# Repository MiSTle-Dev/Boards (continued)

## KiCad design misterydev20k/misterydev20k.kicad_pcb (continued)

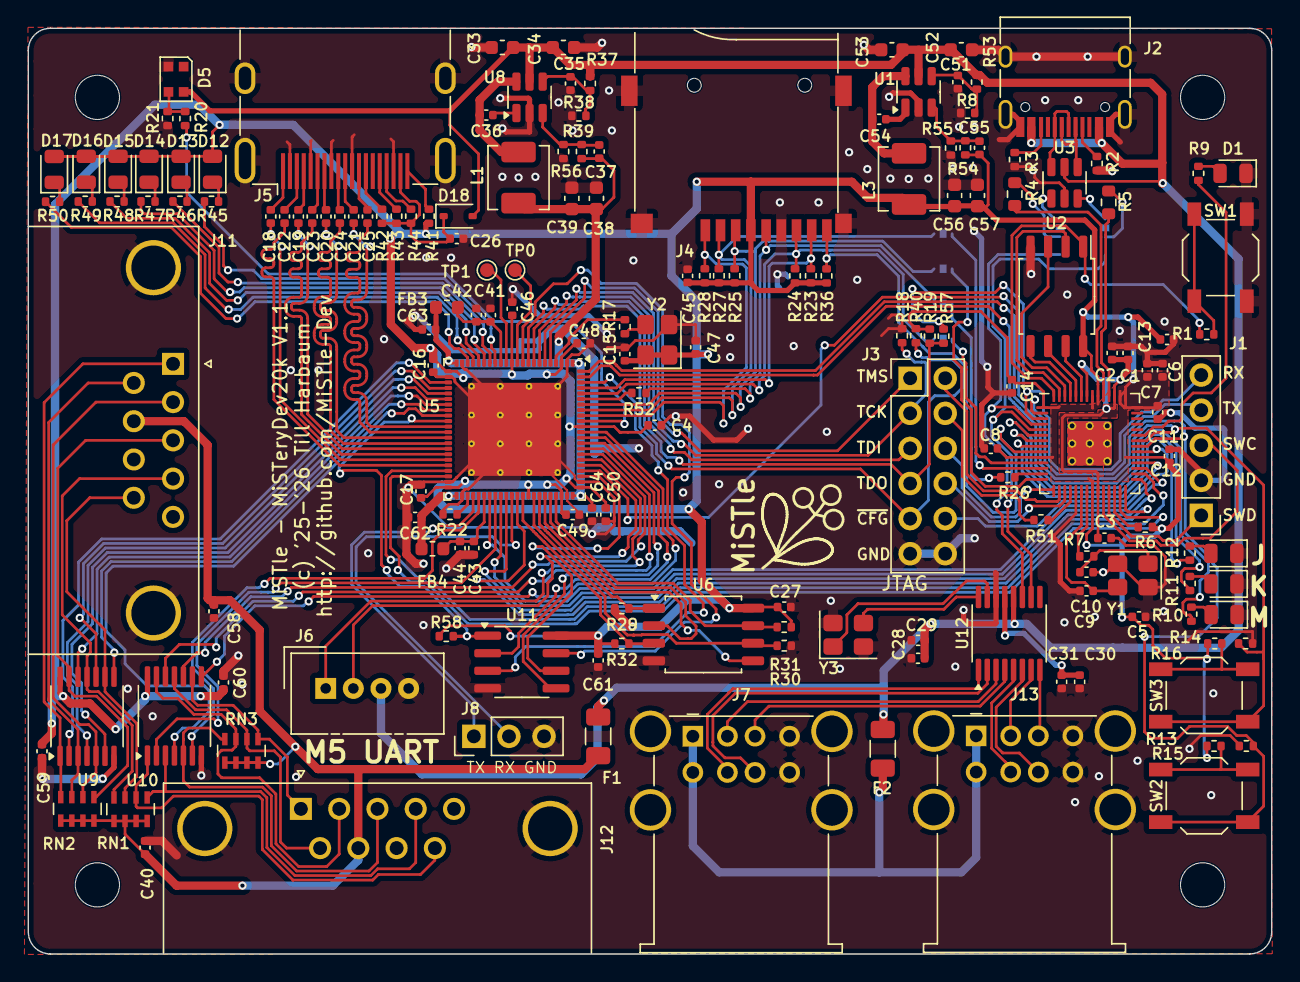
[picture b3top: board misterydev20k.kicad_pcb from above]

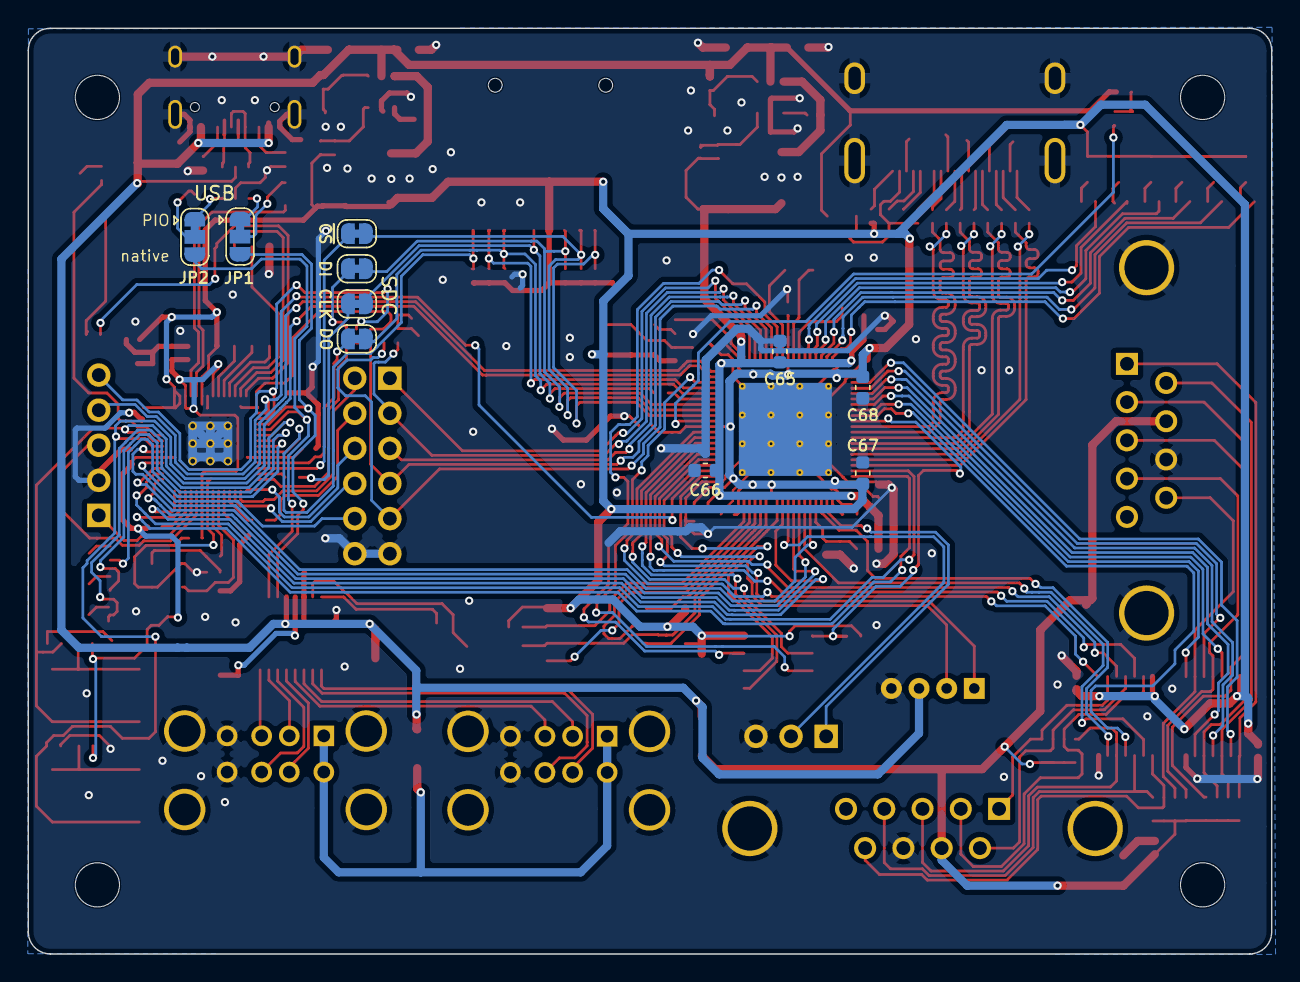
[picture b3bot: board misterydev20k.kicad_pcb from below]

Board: 2 copper layers, 90.0 x 67.0 mm, 183 parts (10 on the bottom side), 177 nets.

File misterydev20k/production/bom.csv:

Designator,Footprint,Quantity,Value,LCSC Part #
"C1, C29, C6, C8",0402,4,1uF,C52923
"C10, C37, C55, C9",0402,4,22pF,C1555
"C11, C12, C13, C14, C15, C16, C17, C18, C19, C2, C20, C21, C22, C23, C24, C25, C26, C27, C28, C3, C30, C35, C36, C4, C40, C42, C44, C45, C46, C47, C48, C49, C5, C50, C51, C54, C58, C59, C60, C61, C62, C63, C64",0402,43,100nF,C1525
"C31, C41, C43, C7",0402,4,10uF,C15525
"C33, C53",0603,2,10uF,C19702
"C34, C39, C52, C57",0603,4,100nF,C14663
"C38, C56",0603,2,22uF,C84419
"D1, D12, D13, D14, D15, D16, D17",0805,7,green,C2297
D18,D_SOD-323,1,1N5819WS,C191023
D2,0805,1,Mouse,C2297
D3,0805,1,Keyboard,C2297
D4,0805,1,Joystick,C2297
D5,LED_WS2812B-2020_PLCC4_2.0x2.0mm,1,WS2812B-2020,C965555
"F1, F2",1206,2,500mA,C70076
"FB3, FB4",0603,2,MPZ1608S101,C107332
J1,PinHeader_1x05_P2.54mm_Vertical,1,SWD,C492404
J11,DSUB-9_Pins_Horizontal_P2.77x2.84mm_EdgePinOffset7.70mm_Housed_MountingHolesOffset9.12mm,1,Joystick 0,C141880
J12,DSUB-9_Pins_Horizontal_P2.77x2.84mm_EdgePinOffset7.70mm_Housed_MountingHolesOffset9.12mm,1,Joystick 1,C141880
"J13, J7",USB_A_Wuerth_61400826021_Horizontal_Stacked,2,USB_A_Stacked,C456021
J2,USB_C_Receptacle_HRO_TYPE-C-31-M-12,1,USB_C_Receptacle_USB2.0,C165948
J3,PinHeader_2x06_P2.54mm_Vertical,1,Jumper block,C32713279
J4,TF-015,1,Micro_SD_Card_Det1,C393941
J5,HDMI_A_Molex_208658-1001_Horizontal,1,HDMI_A,C720616
"L1, L3",L_Sunlord_MWSA0402S,2,3.3uH,C408336
"R1, R15, R16, R30, R6, R7",0402,6,1k,C11702
"R10, R11, R12, R45, R46, R47, R48, R49, R50, R57, R9",0402,11,560,C163460
"R13, R14",0402,2,330,C105875
"R17, R26, R51, R52",0402,4,22,C25092
"R18, R19, R29, R31, R32, R40, R58",0402,7,4k7,C25900
"R2, R3",0402,2,5k1,C25905
R20,0402,1,100,C25076
"R21, R22, R23, R24, R25, R27, R28, R36, R41, R42, R43, R44",0402,12,10k,C25744
"R37, R53",0402,2,47k,C11702
"R38, R8",0402,2,30k,C138008
R39,0402,1,12k 1%,C25752
"R4, R5",0603,2,27R,C25190
R54,0402,1,15k 1%,C25756
R55,0402,1,3k3 1%,C25890
R56,0402,1,18k 1%,C138044
"RN1, RN2, RN3",R_Array_Concave_4x0603,3,10k,C110924
SW1,SW_SPST_TL3342,1,Boot,C318884
SW2,SW_SPST_TL3342,1,KEY1,C318884
SW3,SW_SPST_TL3342,1,KEY2,C318884
"U1, U8",TSOT-23-6,2,SY8113BADC,C78989
"U10, U9",TSSOP-14_4.4x5mm_P0.65mm,2,74LCX07,C2676034
U12,QSOP-16_3.9x4.9mm_P0.635mm,1,CH334R,C4154405
U2,SOIC-8_5.23x5.23mm_P1.27mm,1,W25Q64VS,C131025
U3,SOT-23-6,1,USBLC6-2SC6,C2827654
U4,RP2040-QFN-56,1,RP2040,C2040
U5,ArtInChip_QFN-88-1EP_10x10mm_P0.4mm_EP6.74x6.74mm_ThermalVias,1,GW2AR-LV18-QN88,C9900028472
U6,SOIC-8_5.3x5.3mm_P1.27mm,1,W25Q64JVS,C179171
"Y1, Y3",Crystal_SMD_3225-4Pin_3.2x2.5mm,2,12MHz,C9002
Y2,Crystal_SMD_3225-4Pin_3.2x2.5mm,1,27MHz,C2901577

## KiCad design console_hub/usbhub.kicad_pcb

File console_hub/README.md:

# Console USB Hub

The Tang Console as well as some other Tang Boards need to
be powered via the same USB port that may be used to attach
a USB Hub to e.g. connect keyboards, mice and gamepads for
use in MiSTle retro projects.

This board implements a 4 port USB 2.0 hub and can simultaneously act
as a USB power source to the board. It comes with a USB-C plug and
connects directly to the console to fit nicely along its side without
protruding too much. A USB receptacle allows to power the console
through the Hub.

The board can be manufactured at JLCPCB using the [production data](production).

[Schematic PDF](usbhub_sch.pdf)

Although being designed for the console, the hub also integrates
nicely with the Tang Mega series of boards. Unfortunately it covers the
12V barrel jack there, so the board needs to be powered via
USB through the Hub.

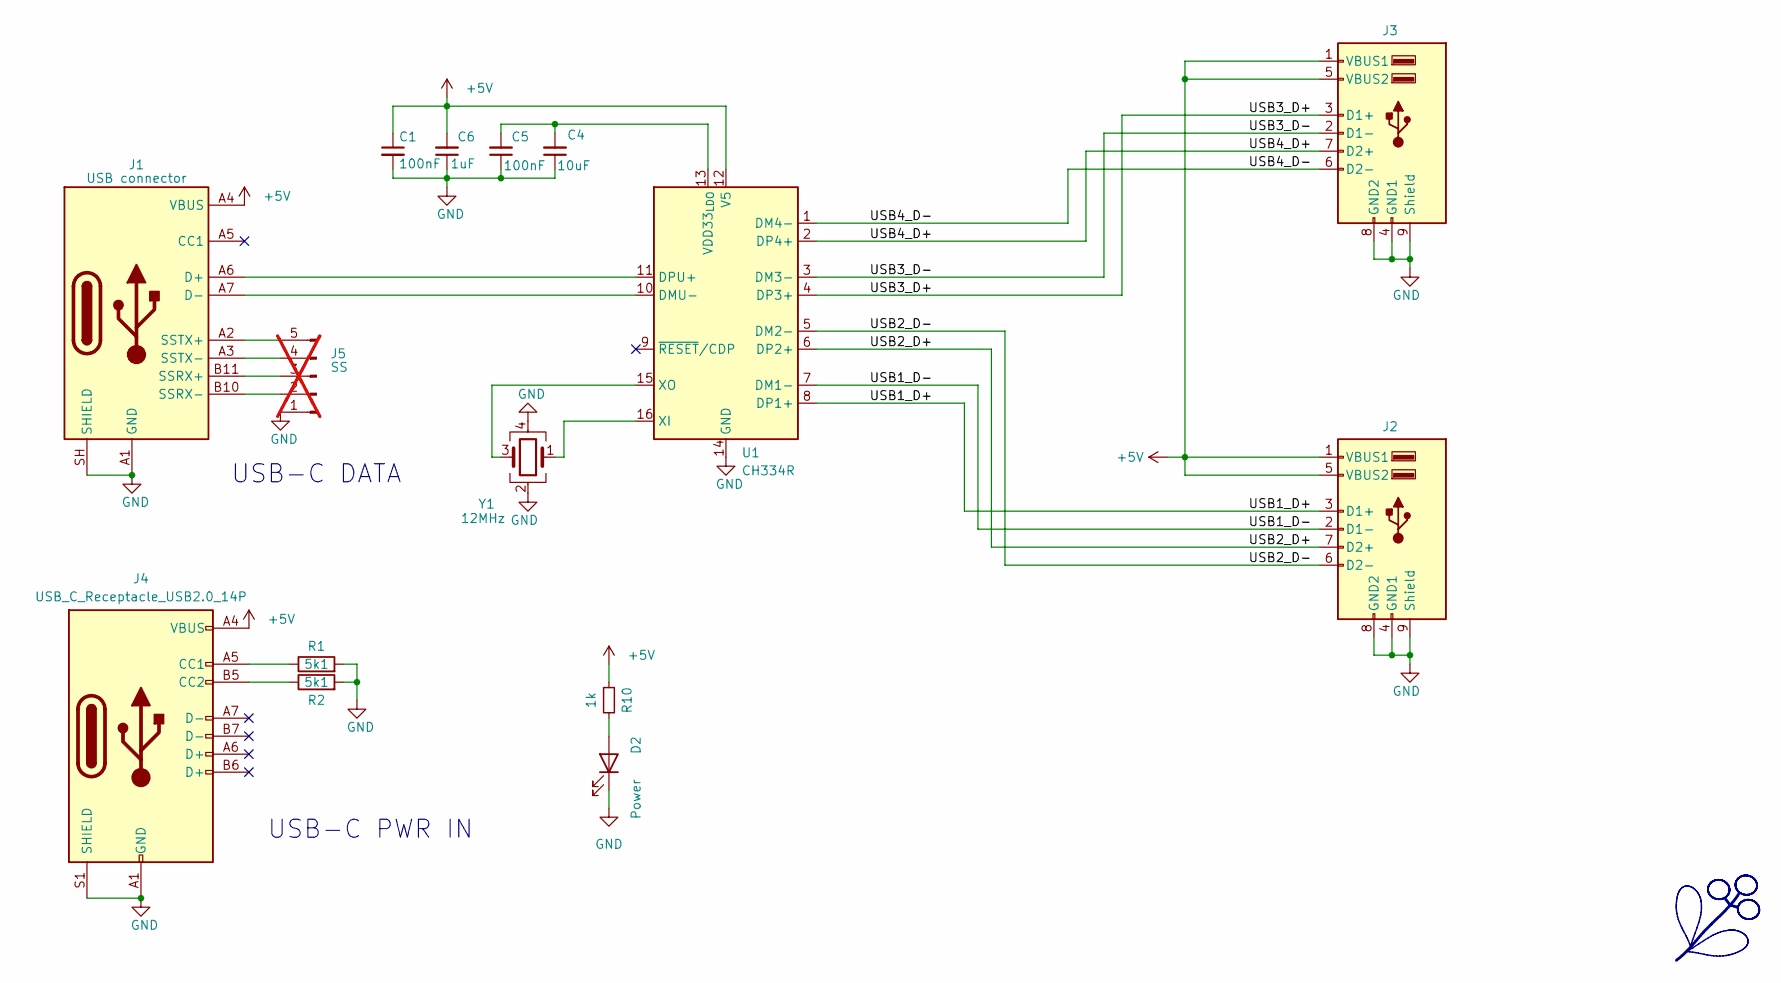
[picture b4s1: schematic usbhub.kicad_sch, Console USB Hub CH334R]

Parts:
C1, C5: 100nF; C_0402_1005Metric; LCSC Part # C1525
C4: 10uF; C_0402_1005Metric; LCSC Part # C15525
C6: 1uF; C_0402_1005Metric; LCSC Part # C52923
D2: Power; LED_0805_2012Metric; LCSC Part # C2297
J1: USB connector; xkb_usb_c_male; LCSC Part # C2879827
J2, J3: USB_A_Stacked; USB_A_Wuerth_61400826021_Horizontal_Stacked; LCSC Part # C456021
J4: USB_C_Receptacle_USB2.0_14P; USB_C_Receptacle_HRO_TYPE-C-31-M-12; LCSC Part # C165948
J5: SS; PinHeader_1x05_P2.54mm_Vertical; not fitted
R1, R2: 5k1; R_0402_1005Metric; LCSC Part # C25905
R10: 1k; R_0402_1005Metric; LCSC Part # C11702
U1: CH334R; QSOP-16_3.9x4.9mm_P0.635mm; LCSC Part # C4154405
Y1: 12MHz; Crystal_SMD_3225-4Pin_3.2x2.5mm; LCSC Part # C9002

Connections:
+5V: C1.1, C6.2, J1.A4 (VBUS), J1.B9 (VBUS), J2.1 (VBUS1), J2.5 (VBUS2), J3.1 (VBUS1), J3.5 (VBUS2), J4.A4 (VBUS), J4.A9 (VBUS), J4.B4 (VBUS), J4.B9 (VBUS), R10.1, U1.12 (V5)
/USB1_D+: J2.3 (D1+), U1.8 (DP1+)
/USB1_D-: J2.2 (D1-), U1.7 (DM1-)
/USB2_D+: J2.7 (D2+), U1.6 (DP2+)
/USB2_D-: J2.6 (D2-), U1.5 (DM2-)
/USB3_D+: J3.3 (D1+), U1.4 (DP3+)
/USB3_D-: J3.2 (D1-), U1.3 (DM3-)
/USB4_D+: J3.7 (D2+), U1.2 (DP4+)
/USB4_D-: J3.6 (D2-), U1.1 (DM4-)
GND: C1.2, C4.1, C5.1, C6.1, D2.1 (K), J1.A1 (GND), J1.A12 (GND), J1.B12 (GND), J1.SH (SHIELD), J2.4 (GND1), J2.8 (GND2), J2.9 (Shield), J3.4 (GND1), J3.8 (GND2), J3.9 (Shield), J4.A1 (GND), J4.A12 (GND), J4.B1 (GND), J4.B12 (GND), J4.S1 (SHIELD), J5.1, R1.2, R2.2, U1.14 (GND), Y1.2, Y1.4
unnamed: D2.2 (A), R10.2
unnamed: J1.A6 (D+), U1.11 (DPU+)
unnamed: J1.A7 (D-), U1.10 (DMU-)
unnamed: J1.B11 (SSRX+), J5.3
unnamed: J1.B10 (SSRX-), J5.2
unnamed: J1.A2 (SSTX+), J5.5
unnamed: J1.A3 (SSTX-), J5.4
unnamed: J4.A5 (CC1), R1.1
unnamed: J4.B5 (CC2), R2.1
unnamed: C4.2, C5.2, U1.13 (VDD33_{LDO})
unnamed: U1.16 (XI), Y1.1
unnamed: U1.15 (XO), Y1.3

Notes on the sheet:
USB-C PWR IN
USB-C DATA

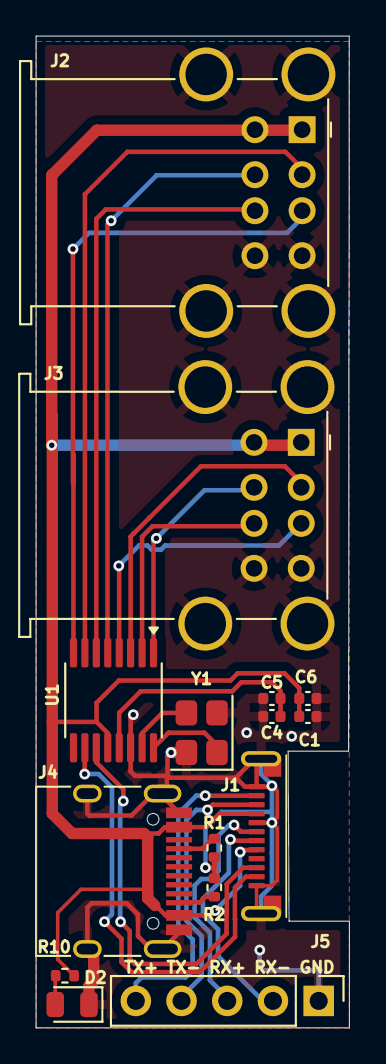
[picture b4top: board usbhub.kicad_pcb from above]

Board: 2 copper layers, 17.4 x 55.1 mm, 15 parts (0 on the bottom side), 22 nets.

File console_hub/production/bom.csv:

Designator,Footprint,Quantity,Value,LCSC Part #
"C1, C5",0402,2,100nF,C1525
C4,0402,1,10uF,C15525
C6,0402,1,1uF,C52923
D2,0805,1,Power,C2297
J1,xkb_usb_c_male,1,USB connector,C2879827
"J2, J3",USB_A_Wuerth_61400826021_Horizontal_Stacked,2,USB_A_Stacked,C456021
J4,USB_C_Receptacle_HRO_TYPE-C-31-M-12,1,USB_C_Receptacle_USB2.0_14P,C165948
"R1, R2",0402,2,5k1,C25905
R10,0402,1,1k,C11702
U1,QSOP-16_3.9x4.9mm_P0.635mm,1,CH334R,C4154405
Y1,Crystal_SMD_3225-4Pin_3.2x2.5mm,1,12MHz,C9002

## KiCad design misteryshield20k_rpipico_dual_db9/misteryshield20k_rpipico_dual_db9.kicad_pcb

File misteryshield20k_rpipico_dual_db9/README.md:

# MiSTeryShield20k RPiPico USB dual DB9 board

The shield is a modification of the original **MiSTeryShield20k RPiPico USB board** by Stefan Voss\
With kind permission & support!  
Manger

**New Features:**

  + 2nd DB9 Joystick port on board
  + on board USB-C power receptacle (incl. fuse and ESD-protection)
  + pin header for case power switch (can be shorted if not needed)
  + Power + FDD + HDD activity LEDs (Red, Yellow, Green)
  + core loading from USB Thumbstick by Stefan Voss (some fine soldering is required!)
  + debug header (Tang & Pi)
  + MIDI optional on M5 Stack connector to be used with  
    e.g. M5 SAM2695 MIDI, or M5 SAM2695 SYNTH

**Features removed:**

  - no spare pin header (the spare pins are used for the 2nd DB9 port)
  - MIDI circuit and DIN connectors (might not be relevant for everyone and have been replaced by an optional external solution)

**Features from the original design:**

- Headers to plug the Tang Nano 20K
- Headers to plug the Raspberry Pi Pico (W)
- Atari / Commodore style joystick interface
- Supports up to two buttons
- Including 5V supply and 5V level shifters
- Works with DB9 joystcks and mice
- MIDI
- 4 x USB-A Interface
- Debug header for Pico UART and e.g. FPGA UART
- 3 x PiPico Status LED (KBD/MOUSE/JOY)
- 3D STEP model to ease case development

**The 2nd DB9 port ist supported by:**

+ MiSTeryNano
+ C64 Nano
+ NanoMig

other cores may follow...

**Current state**

- Schematic Review ✔️
- PCB Review ✔️
- BOM check ✔️
- Preparation of production data ✔️
- Order placement ✔️
- PCB production ✔️
- Assembling ✔️
- Shipping ✔️
- Arrival ✔️
- Testing 🕓

**Test Procedure**

- Tang & PiPico ✔️
- Power circuit ✔️
- Power switch ✔️
- DB9 Port's ✔️
- DB9 Port 1 working with original Amiga Mouse ✔️
- USB-Hub ✔️
- LED Array ✔️
- JTAG wiring ✔️
- PiPico core loader ✔️
- Debug Header ✔️
- Midi-Port 🕓

**Problems**

- Power LED too bright

**JTAG - to enable the core loader, four thin wires must be soldered**

**MIDI - optional on M5 Stack connector to be used with e.g. M5 SAM2695 MIDI, or M5 SAM2695 SYNTH)**

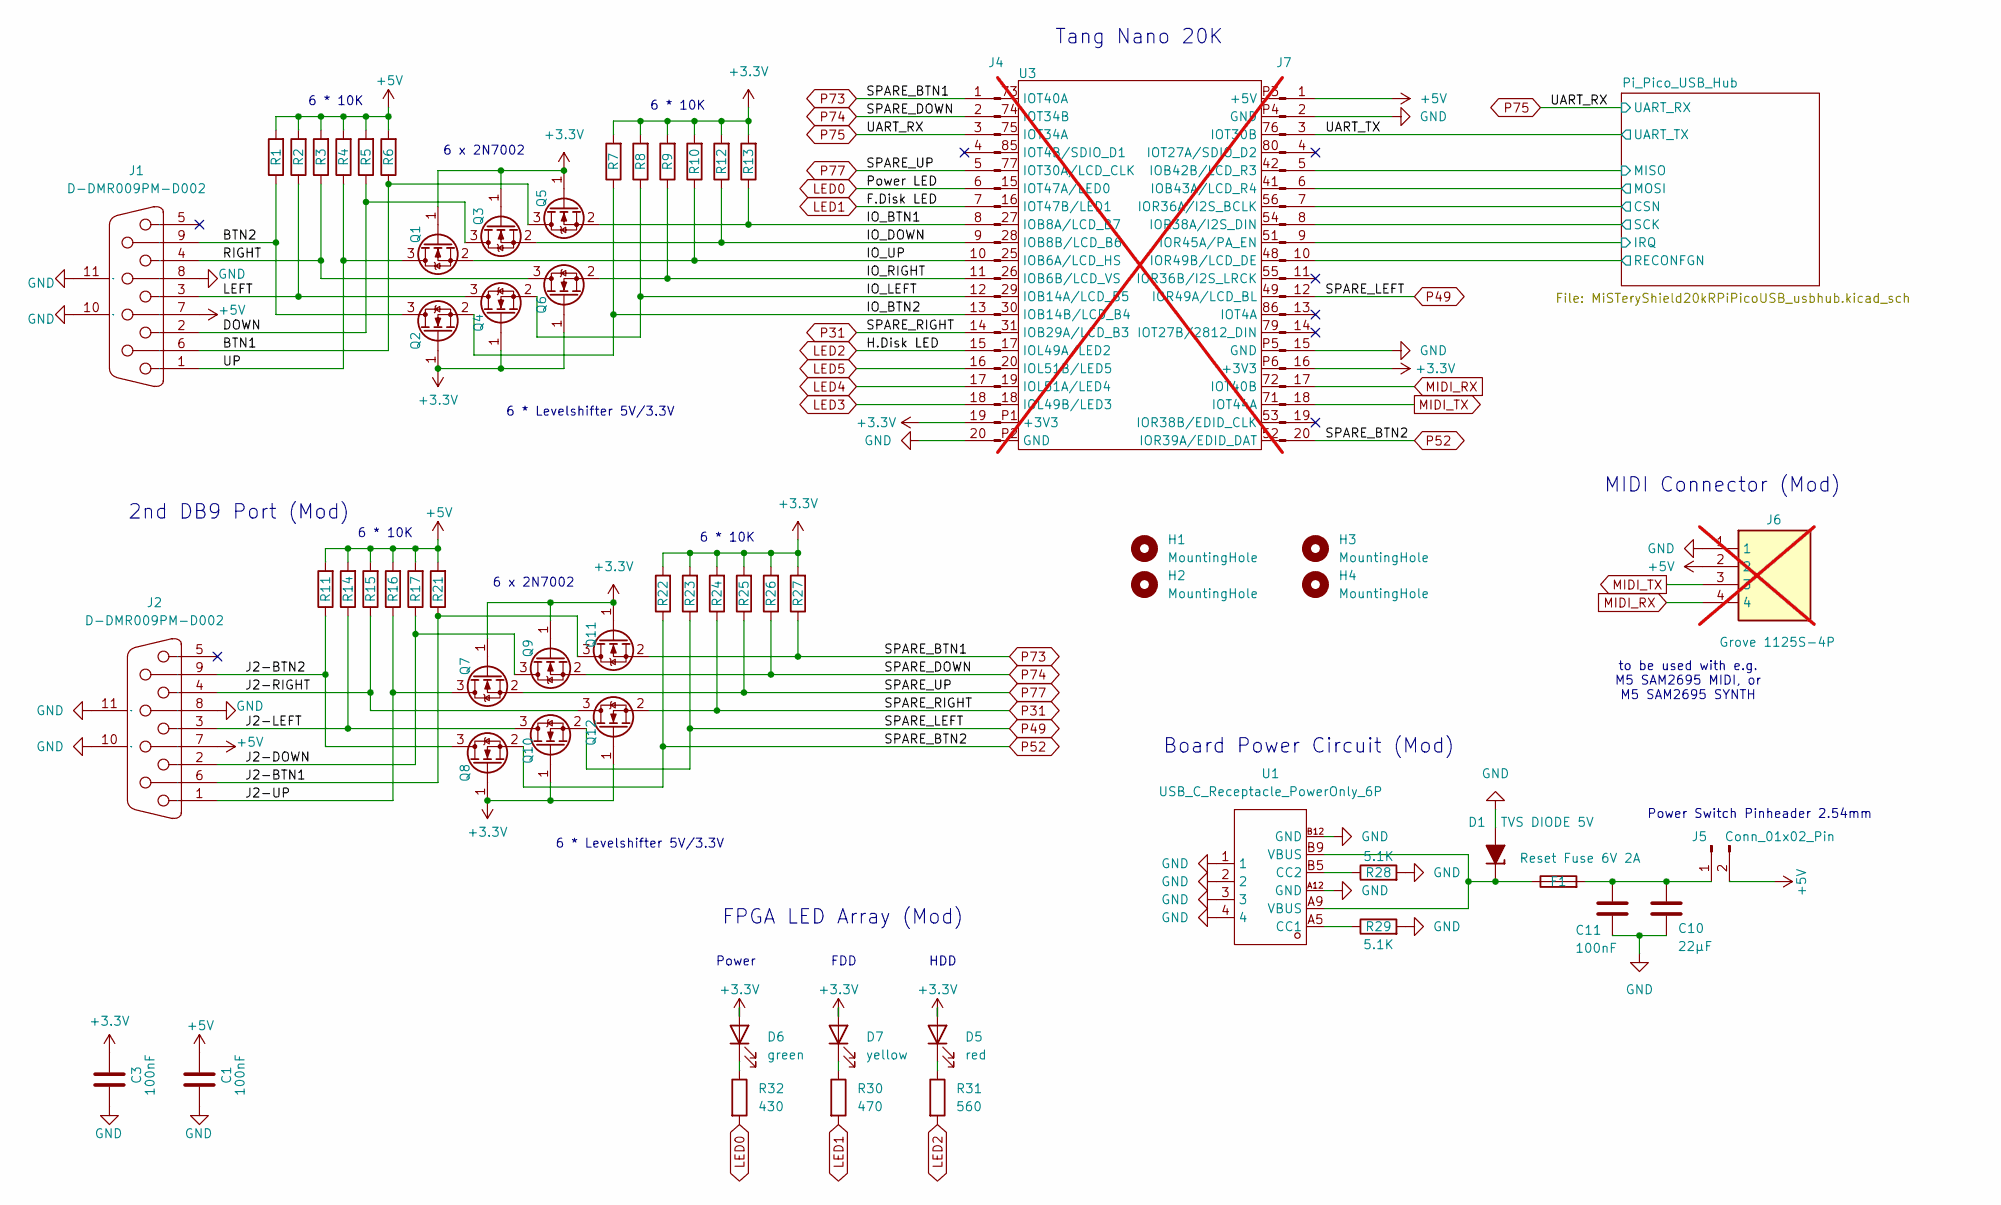
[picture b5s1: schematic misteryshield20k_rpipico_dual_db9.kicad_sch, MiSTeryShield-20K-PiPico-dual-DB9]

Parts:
C1, C3, C11: 100nF; C_0805_2012Metric; LCSC Part # C49678
C10: 22µF; C_0805_2012Metric; LCSC Part # C45783
D1: TVS DIODE 5V; SOD-123_L2.7-W1.6-LS3.7-RD; LCSC Part # C83329
D5: red; LED0805-RD; LCSC Part # C2295
D6: green; LED0805-RD; LCSC Part # C2297
D7: yellow; LED0805-RD; LCSC Part # C2296
F1: Reset Fuse 6V 2A; Fuse_0805_2012Metric; JLCPCB Part # C70158
H1, H2, H3, H4: MountingHole; MountingHole_3.2mm_M3
J1, J2: D-DMR009PM-D002; DSUB-TH_DMR-9P; LCSC Part # C141880
J4, J7: Conn_01x20_Pin; PinSocket_1x20_P2.54mm_Vertical; LCSC Part # C18078139
J5: Conn_01x02_Pin; HDR-TH_2P-P2.54-H-M-W10.4; JLCPCB Part # C492410
J6: Grove 1125S-4P; SHDRRA4W50P0X200_1X4_990X760X480P; Manufacturer_Part_Number S4B-PH-K-S(LF)(SN); Mouser Part Number N/A; not fitted
Q1, Q2, Q3, Q4, Q5, Q6, Q7, Q8, Q9, Q10, Q11, Q12: 2N7002; SOT-23; LCSC Part # C8545
R1, R2, R3, R4, R5, R6, R7, R8, R9, R10, R11, R12, R13, R14, R15, R16, R17, R21, R22, R23, R24, R25, R26, R27: 10k; R_0805_2012Metric; LCSC Part # C17414
R28, R29: 5.1K; R_0805_2012Metric
R30: 470; R_0805_2012Metric; LCSC Part # C17710
R31: 560; R_0805_2012Metric; LCSC Part # C28636
R32: 430; R_0805_2012Metric; LCSC Part # C42000
U1: USB_C_Receptacle_PowerOnly_6P; TYPE-C-SMD_XUNPU_TYPEC-250C-BRP6; Manufacturer Part TYPEC-250C-BRP6; LCSC Part Name Type-C 母 卧贴
U3: TangNano-20K; not fitted

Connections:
+3.3V: C3.2, D5.2 (A), D6.2 (A), D7.2 (A), J4.19, J7.16, Q1.1 (G), Q2.1 (G), Q3.1 (G), Q4.1 (G), Q5.1 (G), Q6.1 (G), Q7.1 (G), Q8.1 (G), Q9.1 (G), Q10.1 (G), Q11.1 (G), Q12.1 (G), R7.2, R8.2, R9.2, R10.2, R12.2, R13.2, R22.2, R23.2, R24.2, R25.2, R26.2, R27.2
+5V: C1.2, J1.7, J2.7, J5.2, J6.2, J7.1, R1.2, R2.2, R3.2, R4.2, R5.2, R6.2, R11.2, R14.2, R15.2, R16.2, R17.2, R21.2; also elsewhere on the board
/BTN1: J1.6, Q5.3 (D), R6.1
/BTN2: J1.9, Q2.3 (D), R1.1
/DOWN: J1.2, Q3.3 (D), R5.1
/IO_BTN1: J4.8, Q5.2 (S), R13.1
/IO_BTN2: J4.13, Q2.2 (S), R7.1
/IO_DOWN: J4.9, Q3.2 (S), R12.1
/IO_LEFT: J4.12, Q4.2 (S), R8.1
/IO_RIGHT: J4.11, Q6.2 (S), R9.1
/IO_UP: J4.10, Q1.2 (S), R10.1
/J2-BTN1: J2.6, Q11.3 (D), R21.1
/J2-BTN2: J2.9, Q8.3 (D), R11.1
/J2-DOWN: J2.2, Q9.3 (D), R17.1
/J2-LEFT: J2.3, Q10.3 (D), R14.1
/J2-RIGHT: J2.4, Q12.3 (D), R15.1
/J2-UP: J2.1, Q7.3 (D), R16.1
/LEFT: J1.3, Q4.3 (D), R2.1
/Pi_Pico_USB_Hub/CSN: J7.7; also elsewhere on the board
/Pi_Pico_USB_Hub/IRQ: J7.9; also elsewhere on the board
/Pi_Pico_USB_Hub/MISO: J7.5; also elsewhere on the board
/Pi_Pico_USB_Hub/MOSI: J7.6; also elsewhere on the board
/Pi_Pico_USB_Hub/RECONFGN: J7.10; also elsewhere on the board
/Pi_Pico_USB_Hub/SCK: J7.8; also elsewhere on the board
/RIGHT: J1.4, Q6.3 (D), R3.1
/UART_TX: J7.3; also elsewhere on the board
/UP: J1.1, Q1.3 (D), R4.1
GND: C1.1, C3.1, C10.2, C11.2, D1.2 (A), J1.8, J1.10 (MH1), J1.11 (MH2), J2.8, J2.10 (MH1), J2.11 (MH2), J4.20, J6.1, J7.2, J7.15, R28.2, R29.2, U1.1, U1.2, U1.3, U1.4, U1.A12 (GND), U1.B12 (GND); also elsewhere on the board
LED0: J4.6, R32.2
LED1: J4.7, R30.2
LED2: J4.15, R31.2
LED3: J4.18
LED4: J4.17
LED5: J4.16
MIDI_RX: J6.4, J7.17
MIDI_TX: J6.3, J7.18
unnamed: D1.1 (K), F1.1, U1.A9 (VBUS), U1.B9 (VBUS)
unnamed: D5.1 (K), R31.1
unnamed: D6.1 (K), R32.1
unnamed: D7.1 (K), R30.1
unnamed: C10.1, C11.1, F1.2, J5.1
unnamed: R29.1, U1.A5 (CC1)
unnamed: R28.1, U1.B5 (CC2)
P31: J4.14, Q12.2 (S), R24.1
P49: J7.12, Q10.2 (S), R23.1
P52: J7.20, Q8.2 (S), R22.1
P73: J4.1, Q11.2 (S), R27.1
P74: J4.2, Q9.2 (S), R26.1
P75: J4.3; also elsewhere on the board
P77: J4.5, Q7.2 (S), R25.1

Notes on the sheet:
Power
Board Power Circuit (Mod)
6 * Levelshifter 5V/3.3V
6 x 2N7002
6 * 10K
HDD
MIDI Connector (Mod)
FDD
Tang Nano 20K
2nd DB9 Port (Mod)
to be used with e.g. M5 SAM2695 MIDI, or M5 SAM2695 SYNTH
Power Switch Pinheader 2.54mm
FPGA LED Array (Mod)

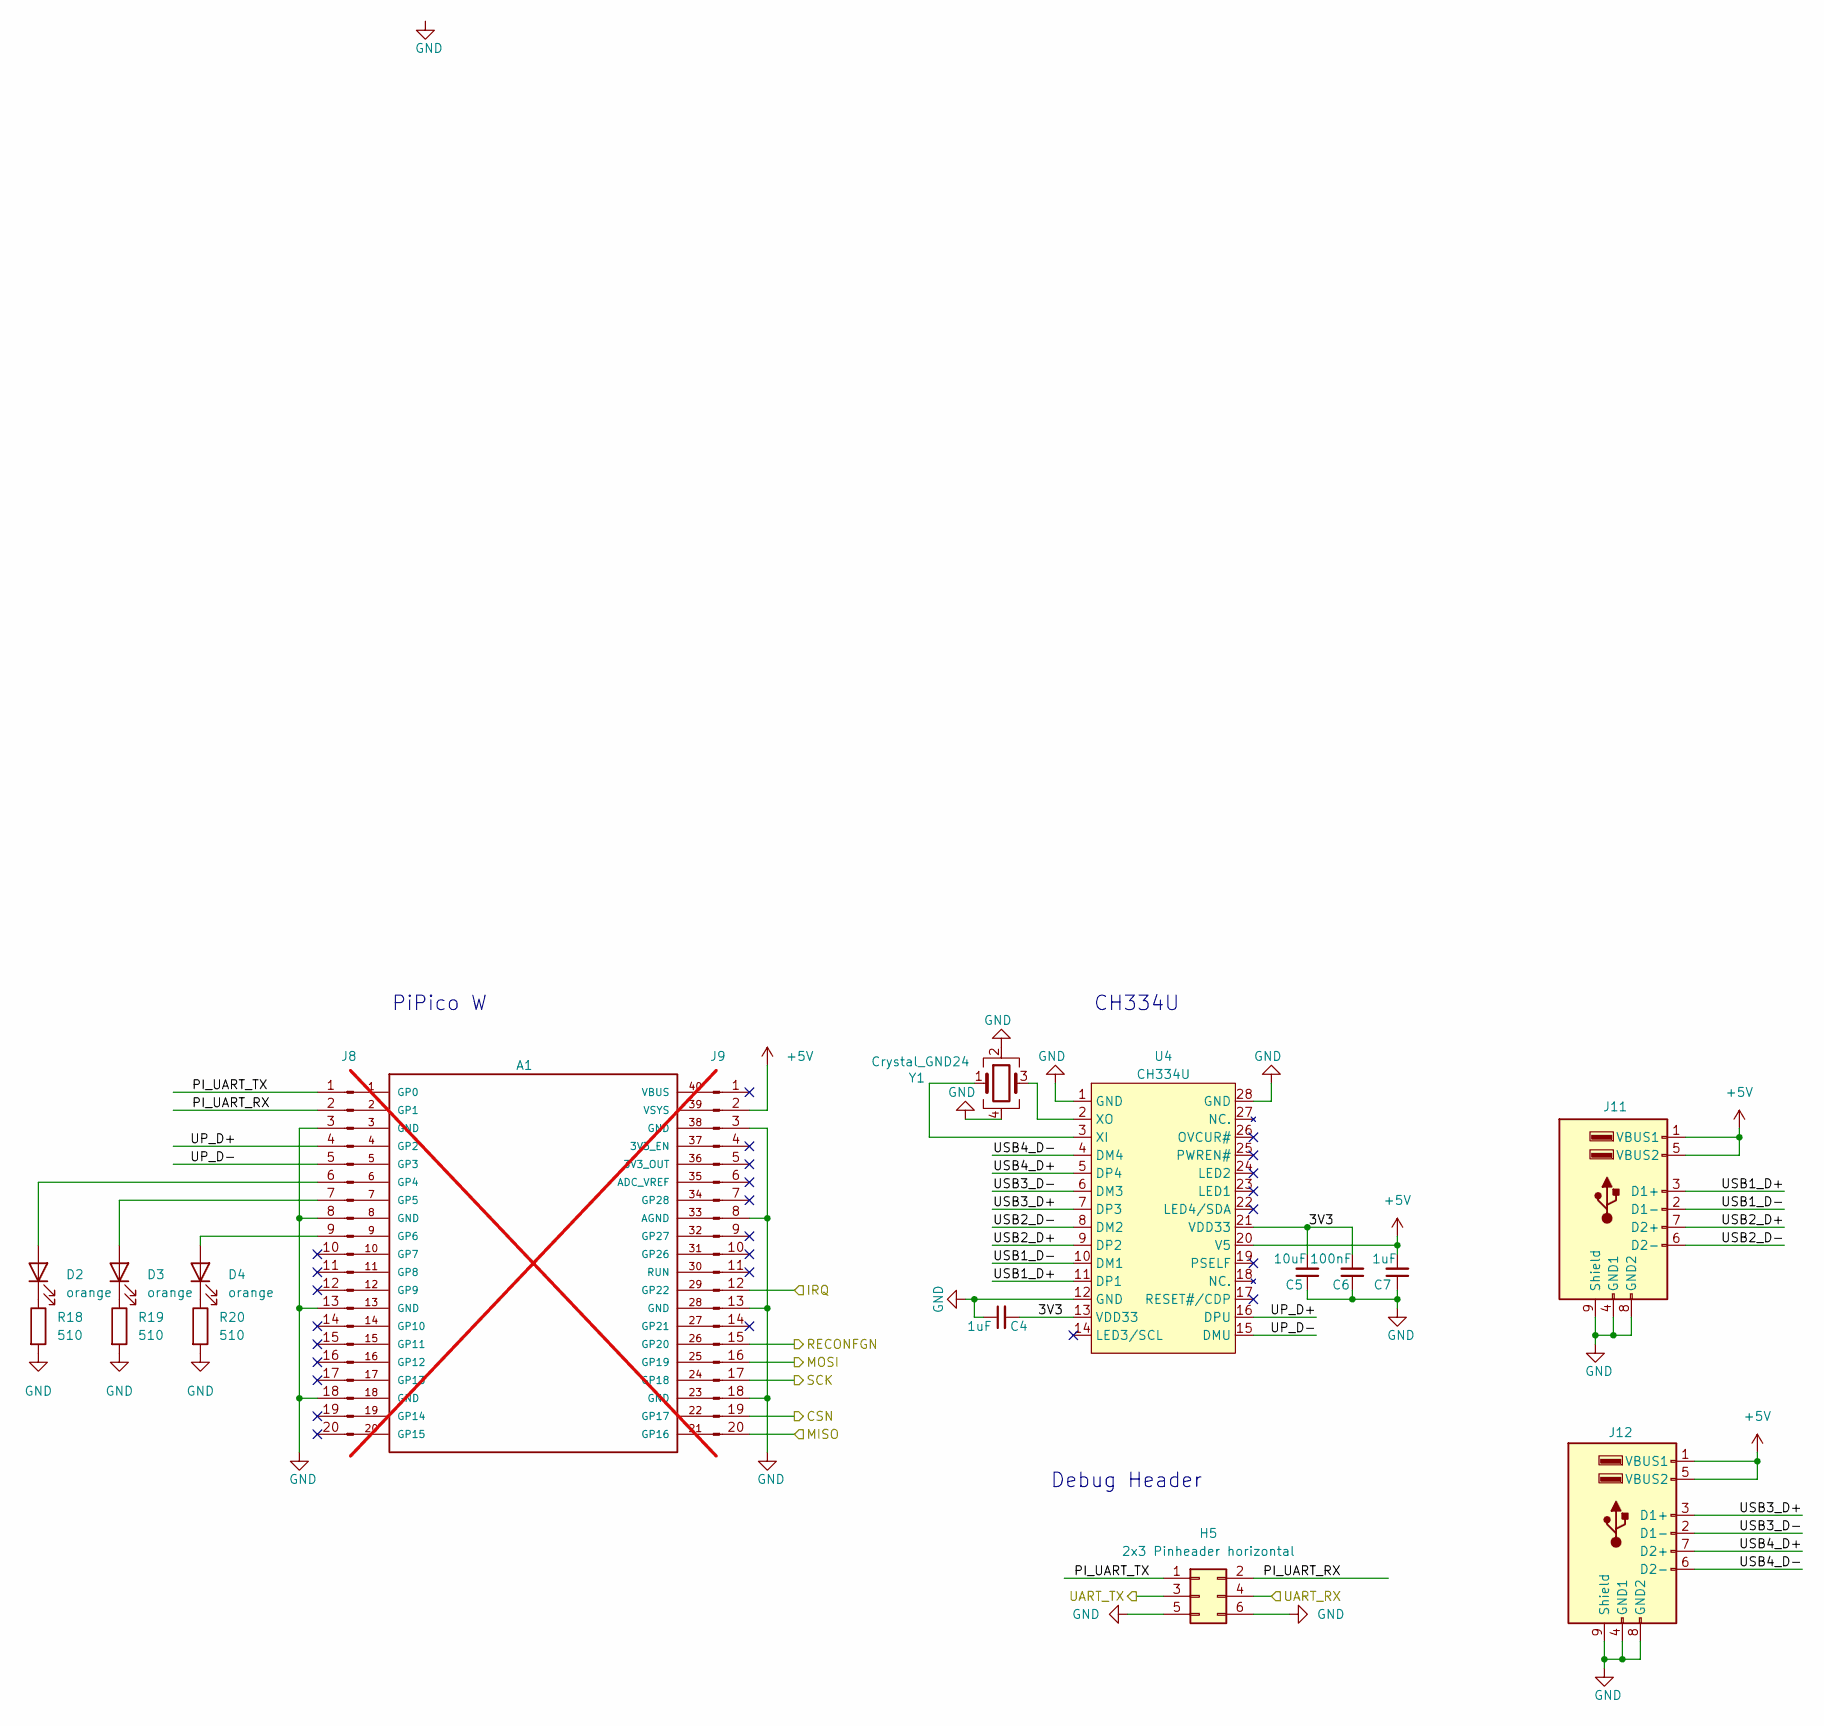
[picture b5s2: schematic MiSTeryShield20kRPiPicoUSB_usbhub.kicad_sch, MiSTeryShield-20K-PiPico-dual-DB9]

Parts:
A1: Raspberry_Pi_Pico_W; not fitted
C4, C7: 1uF; C_0805_2012Metric; LCSC Part # C28323
C5: 10uF; C_0805_2012Metric; LCSC Part # C15850
C6: 100nF; C_0805_2012Metric; LCSC Part # C49678
D2, D3, D4: orange; LED0805-RD; LCSC Part # C110371
H5: 2x3 Pinheader horizontal; HDR-TH_6P-P2.54-H-M-R2-C3-S2.54-W12.3-N; Manufacturer Part PZ254-2-03-W-8.5; JLCPCB Rotation Offset 0
J8: Conn_01x20_Pin; PinSocket_1x20_P2.54mm_Vertical; LCSC Part # C18078139
J9: Conn_01x20_Pin; PinSocket_1x20_P2.54mm_Vertical; JLCPCB Rotation Offset 90
J11, J12: USB_A_Stacked; USB_A_Wuerth_61400826021_Horizontal_Stacked; LCSC Part # C456021
R18, R19, R20: 510; R_0805_2012Metric; LCSC Part # C17734
U4: CH334U; SSOP-28_3.9x9.9mm_P0.635mm; LCSC Part # C5187524
Y1: Crystal_GND24; Crystal_SMD_3225-4Pin_3.2x2.5mm; LCSC Part # C9002

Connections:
+5V: C7.2, J9.2, J11.1 (VBUS1), J11.5 (VBUS2), J12.1 (VBUS1), J12.5 (VBUS2), U4.20 (V5); also elsewhere on the board
/Pi_Pico_USB_Hub/3V3: C4.2, C5.2, C6.2, U4.13 (VDD33), U4.21 (VDD33)
/Pi_Pico_USB_Hub/CSN: J9.19; also elsewhere on the board
/Pi_Pico_USB_Hub/IRQ: J9.12; also elsewhere on the board
/Pi_Pico_USB_Hub/MISO: J9.20; also elsewhere on the board
/Pi_Pico_USB_Hub/MOSI: J9.16; also elsewhere on the board
/Pi_Pico_USB_Hub/PI_UART_RX: H5.2, J8.2
/Pi_Pico_USB_Hub/PI_UART_TX: H5.1, J8.1
/Pi_Pico_USB_Hub/RECONFGN: J9.15; also elsewhere on the board
/Pi_Pico_USB_Hub/SCK: J9.17; also elsewhere on the board
/Pi_Pico_USB_Hub/UP_D+: J8.4, U4.16 (DPU)
/Pi_Pico_USB_Hub/UP_D-: J8.5, U4.15 (DMU)
/Pi_Pico_USB_Hub/USB1_D+: J11.3 (D1+), U4.11 (DP1)
/Pi_Pico_USB_Hub/USB1_D-: J11.2 (D1-), U4.10 (DM1)
/Pi_Pico_USB_Hub/USB2_D+: J11.7 (D2+), U4.9 (DP2)
/Pi_Pico_USB_Hub/USB2_D-: J11.6 (D2-), U4.8 (DM2)
/Pi_Pico_USB_Hub/USB3_D+: J12.3 (D1+), U4.7 (DP3)
/Pi_Pico_USB_Hub/USB3_D-: J12.2 (D1-), U4.6 (DM3)
/Pi_Pico_USB_Hub/USB4_D+: J12.7 (D2+), U4.5 (DP4)
/Pi_Pico_USB_Hub/USB4_D-: J12.6 (D2-), U4.4 (DM4)
/UART_TX: H5.3; also elsewhere on the board
GND: C4.1, C5.1, C6.1, C7.1, H5.5, H5.6, J8.3, J8.8, J8.13, J8.18, J9.3, J9.8, J9.13, J9.18, J11.4 (GND1), J11.8 (GND2), J11.9 (Shield), J12.4 (GND1), J12.8 (GND2), J12.9 (Shield), R18.2, R19.2, R20.2, U4.1 (GND), U4.12 (GND), U4.28 (GND), Y1.2, Y1.4; also elsewhere on the board
unnamed: D2.2 (A), J8.6
unnamed: D2.1 (K), R18.1
unnamed: D3.2 (A), J8.7
unnamed: D3.1 (K), R19.1
unnamed: D4.2 (A), J8.9
unnamed: D4.1 (K), R20.1
unnamed: U4.3 (XI), Y1.1
unnamed: U4.2 (XO), Y1.3
P75: H5.4; also elsewhere on the board

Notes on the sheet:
CH334U
PiPico W
Debug Header

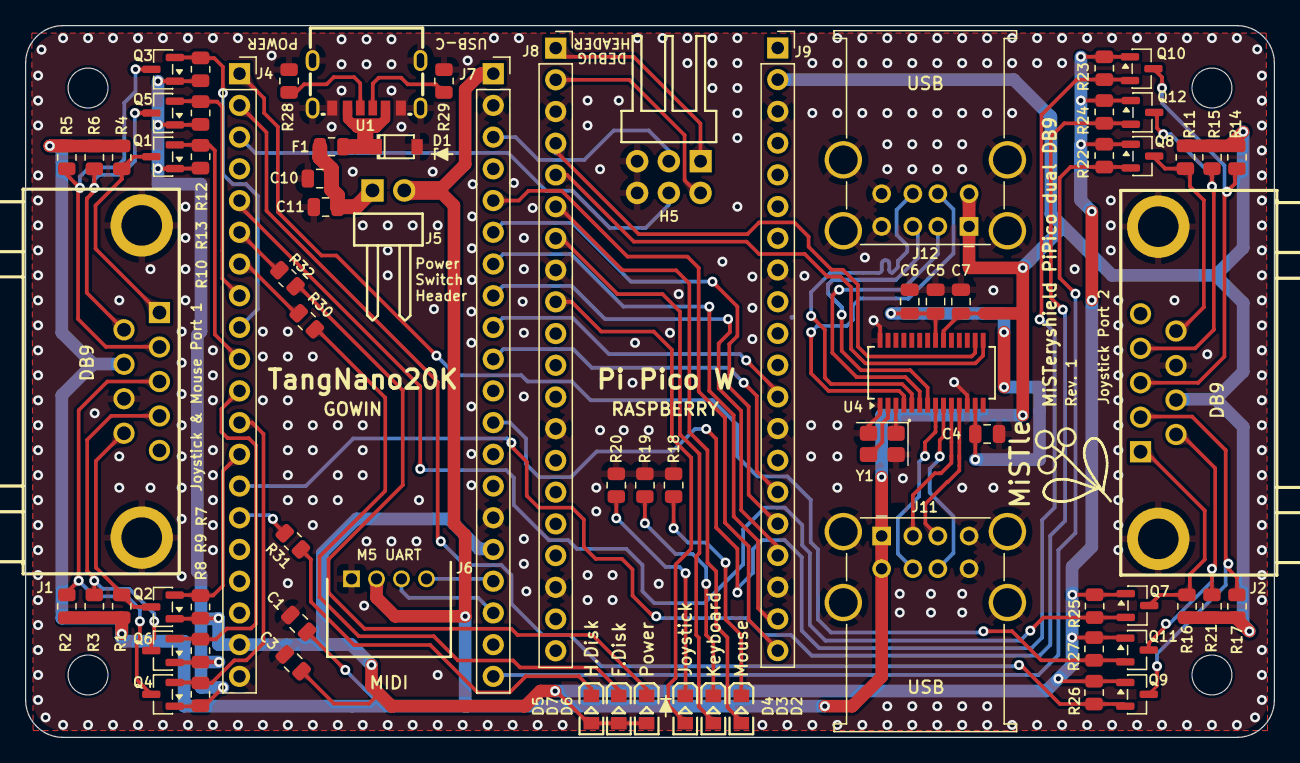
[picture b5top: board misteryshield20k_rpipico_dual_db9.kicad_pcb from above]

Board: 2 copper layers, 100.0 x 57.0 mm, 78 parts (0 on the bottom side), 68 nets.

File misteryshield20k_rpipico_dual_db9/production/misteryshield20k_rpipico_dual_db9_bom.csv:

Designator,Footprint,Quantity,Value,LCSC Part #
"C1, C11, C3, C6",0805,4,100nF,C49678
C10,0805,1,22µF,C45783
"C4, C7",0805,2,1uF,C28323
C5,0805,1,10uF,C15850
D1,SOD-123_L2.7-W1.6-LS3.7-RD,1,TVS DIODE 5V,C83329
"D2, D3, D4",LED0805-RD,3,orange, C110371
D5,LED0805-RD,1,red, C2295
D6,LED0805-RD,1,green,C2297
D7,LED0805-RD,1,yellow, C2296
F1,0805,1,Reset Fuse 6V 2A,C70158
H5,HDR-TH_6P-P2.54-H-M-R2-C3-S2.54-W12.3-N,1,2x3 Pinheader horizontal,C2894983
"J1, J2",DSUB-TH_DMR-9P,2,D-DMR009PM-D002,
"J11, J12",USB_A_Wuerth_61400826021_Horizontal_Stacked,2,USB_A_Stacked,C456021
"J4, J7, J8, J9",PinSocket_1x20_P2.54mm_Vertical,4,Conn_01x20_Pin,C18078139
J5,HDR-TH_2P-P2.54-H-M-W10.4,1,Conn_01x02_Pin,C492410
"Q1, Q10, Q11, Q12, Q2, Q3, Q4, Q5, Q6, Q7, Q8, Q9",SOT-23,12,2N7002,C8545
"R1, R10, R11, R12, R13, R14, R15, R16, R17, R2, R21, R22, R23, R24, R25, R26, R27, R3, R4, R5, R6, R7, R8, R9",0805,24,10k,C17414
"R18, R19, R20",0805,3,510,C17734
"R28, R29",0805,2,5.1K,
R30,0805,1,470,C17710
R31,0805,1,560,C28636
R32,0805,1,430,C42000
U1,TYPE-C-SMD_XUNPU_TYPEC-250C-BRP6,1,USB_C_Receptacle_PowerOnly_6P,C5374812
U4,SSOP-28_3.9x9.9mm_P0.635mm,1,CH334U,C5187524
Y1,Crystal_SMD_3225-4Pin_3.2x2.5mm,1,Crystal_GND24,C9002
